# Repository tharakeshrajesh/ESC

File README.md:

# ESC
A probably not working electronic speed controller for a brushless direct current motor. <br>
It is rated for 12V and 20A (probably). <br>
<br>
__IT IS CURRENTLY UNTESTED SO TEST IT AT YOUR OWN WILL.__ <br>
<br>
I recommend reading all the README in each folder. **They are not all the same.**

## Some other info
This is a custom ESC made from scratch including a MOSFET half-bridge meant for brushless DC motors. Switches phases at high speeds. It takes in 12v and 20a from an XT60 male connector. You can program the STM microcontroller using the SWD header pins located on the board. There are two status LEDs (one on each side) to help with debugging if needed. The LED on the back of the board (D1) is connected to the gate driver fault pins so it will turn on if there is an error with the gate driver. The LED on the front (D3) is connected to the STM32 micocontroller and can be programmed for debugging or something (connected to pin 40). There are NO phase pads or bullet connectors located on the board for this revision so you will need to use alligator clips or something on the MOSFET source pins/body.

# Schematics

# PCB Previews

# Contact
email -> trajesh@3272010.xyz

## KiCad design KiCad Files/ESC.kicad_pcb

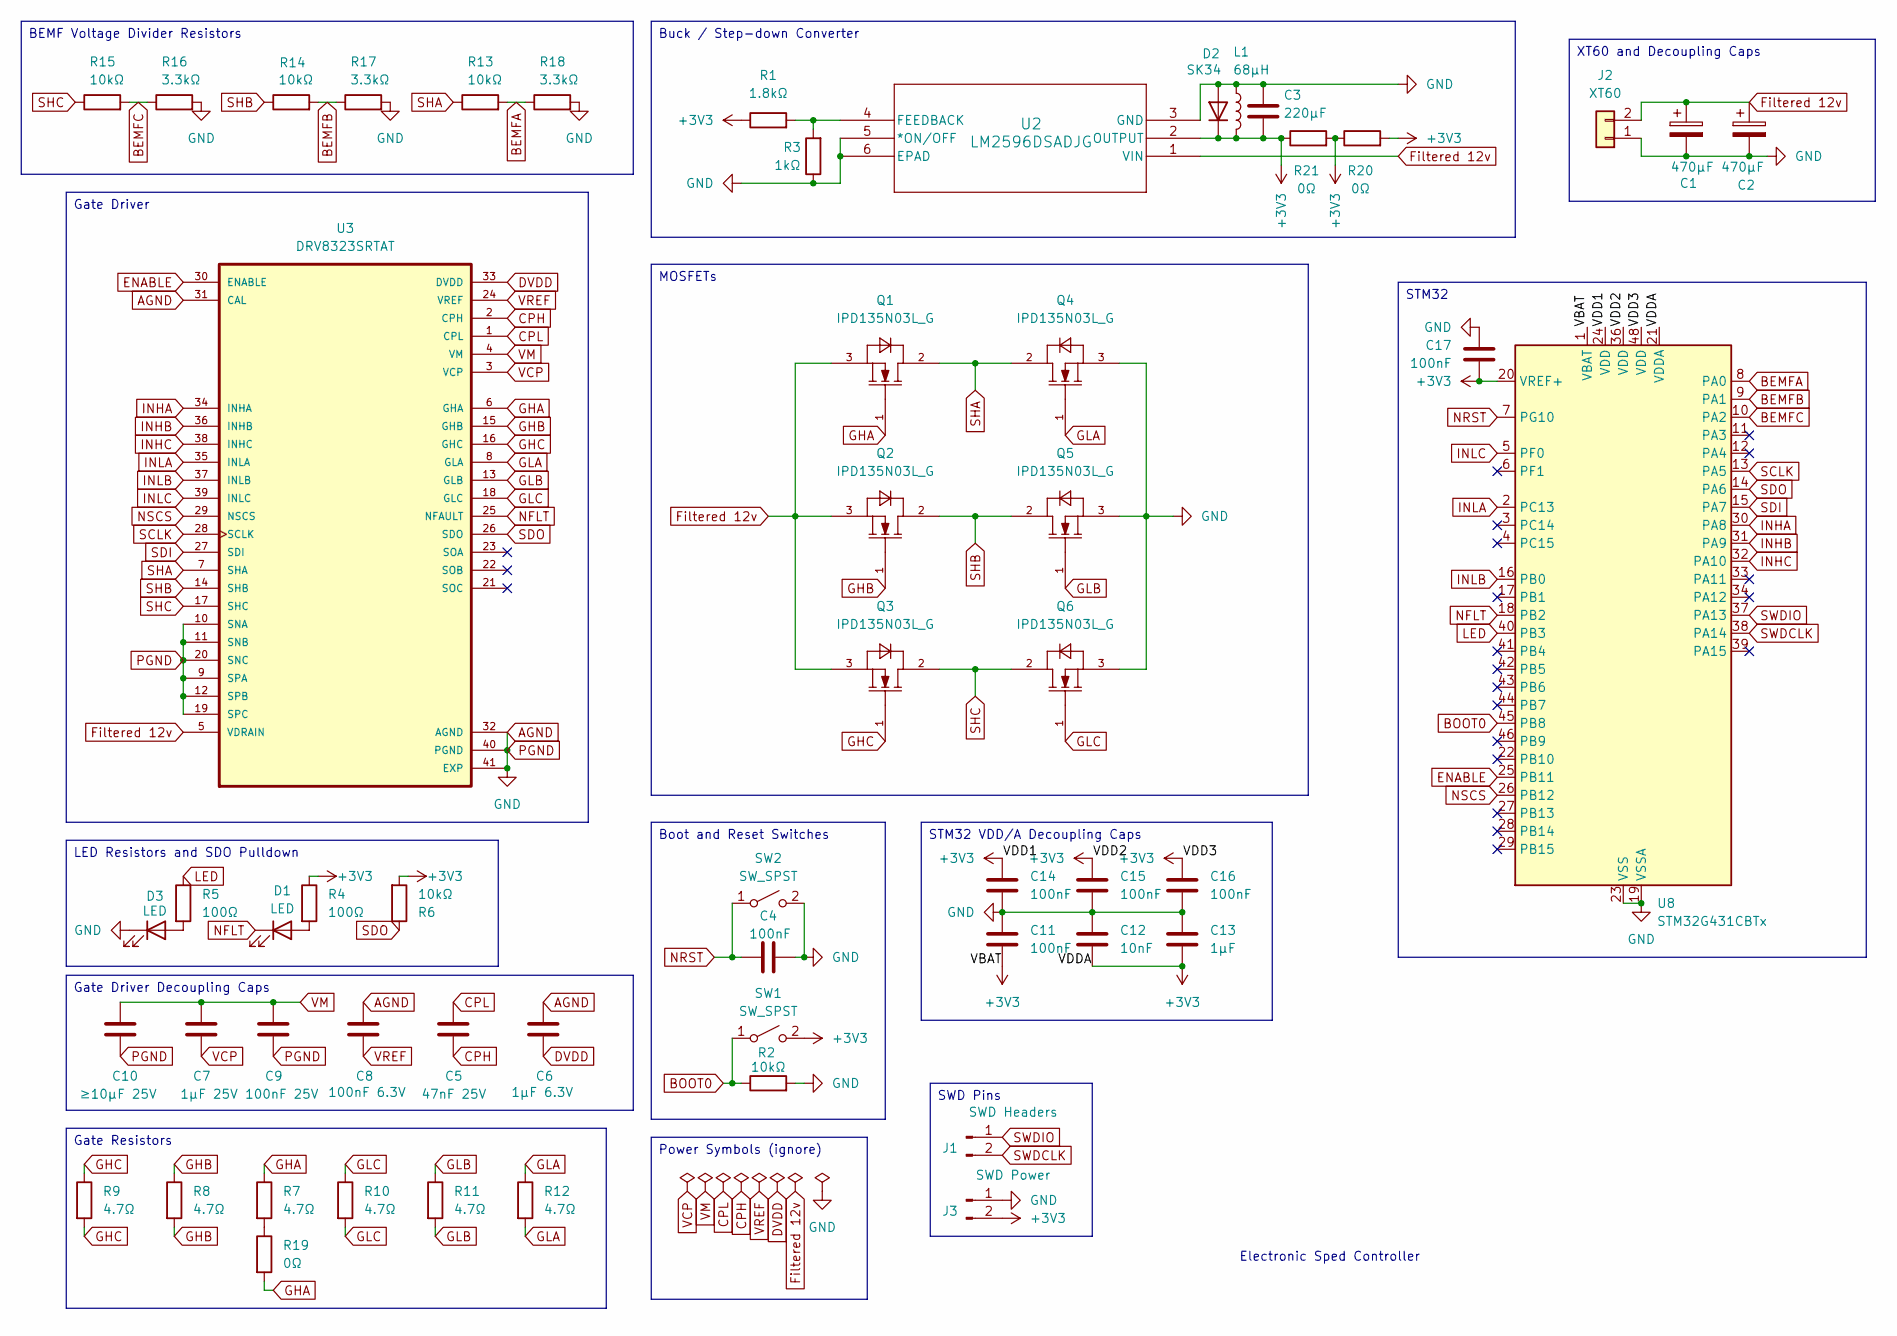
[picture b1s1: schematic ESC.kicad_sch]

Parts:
C1, C2: 470µF; CAP_ZSU_G16_PAN
C3: 220µF; C_1206_3216Metric
C4, C11, C14, C15, C16, C17: 100nF; C_0402_1005Metric
C5: 47nF 25V; C_0402_1005Metric
C6: 1µF 6.3V; C_0402_1005Metric
C7: 1µF 25V; C_0402_1005Metric
C8: 100nF 6.3V; C_0402_1005Metric
C9: 100nF 25V; C_0402_1005Metric
C10: ≥10µF 25V; C_0805_2012Metric
C12: 10nF; C_0603_1608Metric
C13: 1µF; C_0402_1005Metric
D1, D3: LED; LED_0603_1608Metric
D2: SK34; D_SMC
J1: SWD Headers; PinHeader_1x02_P2.54mm_Vertical
J2: XT60; AMASS_XT60PW-M_1x02_P7.20mm_Horizontal
J3: SWD Power; PinHeader_1x02_P2.54mm_Vertical
L1: 68µH; L_Bourns_SRR1260
Q1, Q2, Q3, Q4, Q5, Q6: IPD135N03L_G; TO228P998X235-3N-2-V
R1: 1.8kΩ; R_0603_1608Metric
R2, R6, R13, R14, R15: 10kΩ; R_0603_1608Metric
R3: 1kΩ; R_0603_1608Metric
R4, R5: 100Ω; R_0603_1608Metric
R7, R8, R9, R10, R11, R12: 4.7Ω; R_0402_1005Metric
R16, R17, R18: 3.3kΩ; R_0603_1608Metric
R19, R20, R21: 0Ω; R_0805_2012Metric
SW1, SW2: SW_SPST; SW_SPST_TL3305B
U2: LM2596DSADJG; D2PAK-5_ONS
U3: DRV8323SRTAT; QFN50P600X600X80-41N415X415; DigiKey_Part_Number 296-47095-1-ND
U8: STM32G431CBTx; LQFP48-7x7mm

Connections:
+3V3: C3.2, C11.2, C12.2, C13.2, C14.1, C15.1, C16.1, C17.1, D2.1 (K), J3.2, L1.2, R1.1, R4.1, R6.2, R20.1, R20.2, R21.1, R21.2, SW1.2 (B), U2.2 (OUTPUT), U8.1 (VBAT), U8.20 (VREF+), U8.21 (VDDA), U8.24 (VDD), U8.36 (VDD), U8.48 (VDD)
AGND: C1.2, C2.2, C3.1, C4.2, C6.1, C8.1, C9.2, C10.2, C11.1, C12.1, C13.1, C14.2, C15.2, C16.2, C17.2, D2.2 (A), D3.1 (K), J2.1, J3.1, L1.1, Q4.3, Q5.3, Q6.3, R2.2, R3.1, R16.2, R17.2, R18.2, SW2.2 (B), U2.3 (GND), U2.5 (*ON/OFF), U2.6 (EPAD), U3.9 (SPA), U3.10 (SNA), U3.11 (SNB), U3.12 (SPB), U3.19 (SPC), U3.20 (SNC), U3.31 (CAL), U3.32 (AGND), U3.40 (PGND), U3.41 (EXP), U8.19 (VSSA), U8.23 (VSS), U8.35 (VSS), U8.47 (VSS)
BEMFA: R13.2, R18.1, U8.8 (PA0)
BEMFB: R14.2, R17.1, U8.9 (PA1)
BEMFC: R15.2, R16.1, U8.10 (PA2)
BOOT0: R2.1, SW1.1 (A), U8.45 (PB8)
CPH: C5.2, U3.2 (CPH)
CPL: C5.1, U3.1 (CPL)
DVDD: C6.2, U3.33 (DVDD)
ENABLE: U3.30 (ENABLE), U8.25 (PB11)
Filtered 12v: C1.1, C2.1, J2.2, Q1.3, Q2.3, Q3.3, U2.1 (VIN), U3.5 (VDRAIN)
GHB: Q2.1, R8.1, R8.2, U3.15 (GHB)
GHC: Q3.1, R9.1, R9.2, U3.16 (GHC)
GLA: Q4.1, R12.1, R12.2, U3.8 (GLA)
GLB: Q5.1, R11.1, R11.2, U3.13 (GLB)
GLC: Q6.1, R10.1, R10.2, U3.18 (GLC)
INHA: U3.34 (INHA), U8.30 (PA8)
INHB: U3.36 (INHB), U8.31 (PA9)
INHC: U3.38 (INHC), U8.32 (PA10)
INLA: U3.35 (INLA), U8.2 (PC13)
INLB: U3.37 (INLB), U8.16 (PB0)
INLC: U3.39 (INLC), U8.5 (PF0)
LED: R5.1, U8.40 (PB3)
NFLT: D1.1 (K), U3.25 (NFAULT), U8.18 (PB2)
NRST: C4.1, SW2.1 (A), U8.7 (PG10)
NSCS: U3.29 (NSCS), U8.26 (PB12)
unnamed: D1.2 (A), R4.2
unnamed: D3.2 (A), R5.2
unnamed: R7.2, R19.1
unnamed: R1.2, R3.2, U2.4 (FEEDBACK)
SCLK: U3.28 (SCLK), U8.13 (PA5)
SDI: U3.27 (SDI), U8.15 (PA7)
SDO: R6.1, U3.26 (SDO), U8.14 (PA6)
SHA: Q1.2, Q4.2, R13.1, U3.7 (SHA)
SHB: Q2.2, Q5.2, R14.1, U3.14 (SHB)
SHC: Q3.2, Q6.2, R15.1, U3.17 (SHC)
SWDCLK: J1.2, U8.38 (PA14)
SWDIO: J1.1, U8.37 (PA13)
VCP: C7.2, U3.3 (VCP)
VM: C7.1, C9.1, C10.1, U3.4 (VM)
VREF: C8.2, U3.24 (VREF)

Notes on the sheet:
Electronic Sped Controller
XT60 and Decoupling Caps
Boot and Reset Switches
SWD Pins
Gate Resistors
STM32 VDD/A Decoupling Caps
STM32
MOSFETs
Buck / Step-down Converter
BEMF Voltage Divider Resistors
Power Symbols (ignore)
Gate Driver Decoupling Caps
LED Resistors and SDO Pulldown
Gate Driver

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
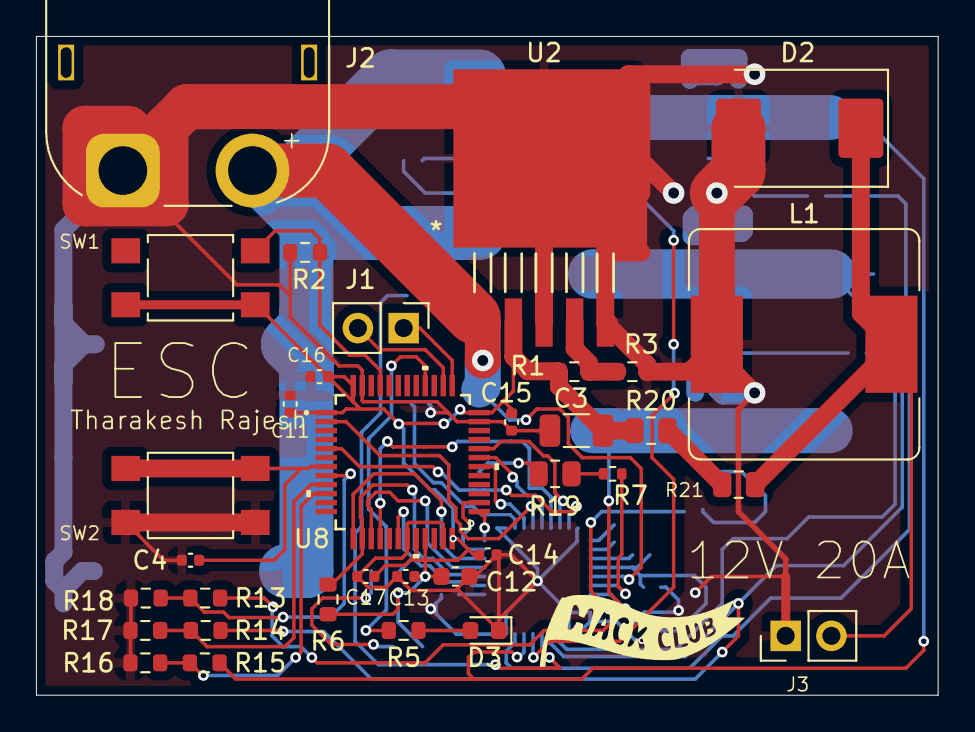
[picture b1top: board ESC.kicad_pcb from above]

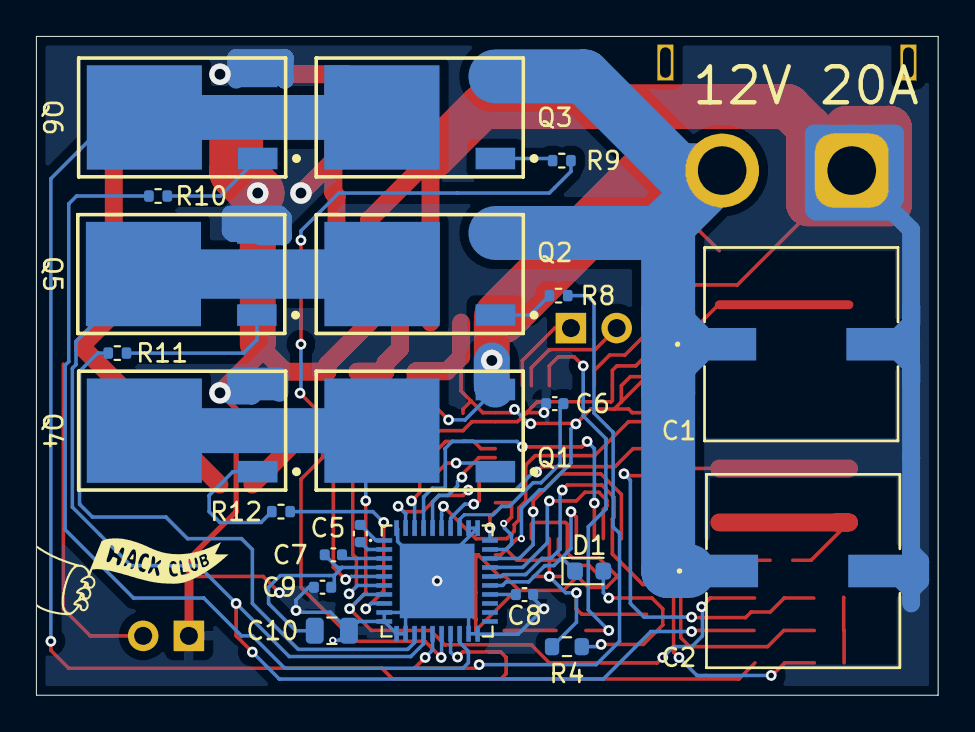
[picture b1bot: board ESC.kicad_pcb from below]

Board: 2 copper layers, 50.1 x 36.6 mm, 56 parts (22 on the bottom side), 43 nets.

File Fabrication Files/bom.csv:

Designator,Footprint,Quantity,Value,LCSC Part #
"C1, C2",CAP_ZSU_G16_PAN,2,470µF,C403803
C10,0805,1,≥10µF 25V,
"C11, C14, C15, C16, C17, C4",0402,6,100nF,C466234
C12,0603,1,10nF,
C13,0402,1,1µF,
C3,1206,1,220µF,
C5,0402,1,47nF 25V,
C6,0402,1,1µF 6.3V,
C7,0402,1,1µF 25V,
C8,0402,1,100nF 6.3V,
C9,0402,1,100nF 25V,
"D1, D3",0603,2,LED,
D2,D_SMC,1,SK34,C260396
J1,PinHeader_1x02_P2.54mm_Vertical,1,SWD Headers,
J2,AMASS_XT60PW-M_1x02_P7.20mm_Horizontal,1,XT60,
J3,PinHeader_1x02_P2.54mm_Vertical,1,SWD Power,
L1,L_Bourns_SRR1260,1,68µH,
"Q1, Q2, Q3, Q4, Q5, Q6",TO228P998X235-3N-2-V,6,IPD135N03L_G,C152614
R1,0603,1,1.8kΩ,
"R10, R11, R12, R7, R8, R9",0402,6,4.7Ω,
"R13, R14, R15, R2, R6",0603,5,10kΩ,
"R16, R17, R18",0603,3,3.3kΩ,
"R19, R20, R21",0805,3,0Ω,
R3,0603,1,1kΩ,
"R4, R5",0603,2,100Ω,
"SW1, SW2",SW_SPST_TL3305B,2,SW_SPST,C2886900
U2,D2PAK-5_ONS,1,LM2596DSADJG,C7419983
U3,QFN50P600X600X80-41N415X415,1,DRV8323SRTAT,C2150452
U8,LQFP48-7x7mm,1,STM32G431CBTx,C529355

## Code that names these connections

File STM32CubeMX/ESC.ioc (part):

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Mcu.Name=STM32G431C(6-8-B)Tx
Mcu.Package=LQFP48
Mcu.UserName=STM32G431CBTx
PA0.Mode=IN1-Single-Ended
PA0.Signal=ADC1_IN1
PA1.Mode=IN2-Single-Ended
PA1.Signal=ADC1_IN2
PA10.Signal=S_TIM1_CH3
PA11.Signal=S_TIM1_CH4
PA2.Mode=IN3-Single-Ended
PA2.Signal=ADC1_IN3
PA5.Mode=Full_Duplex_Master
PA5.Signal=SPI1_SCK
PA6.Mode=Full_Duplex_Master
PA6.Signal=SPI1_MISO
PA7.Mode=Full_Duplex_Master
PA7.Signal=SPI1_MOSI
PA8.Signal=S_TIM1_CH1
PA9.Signal=S_TIM1_CH2
PB0.Mode=Output Compare2 CH2 CH2N
PB0.Signal=TIM1_CH2N
PB12.Signal=GPIO_Output
PB13.Signal=GPIO_Output
PB2.Signal=GPIO_Input
PB3.Signal=GPIO_Output
PC13.GPIOParameters=GPIO_ModeDefaultPP,GPIO_Speed
PC13.GPIO_ModeDefaultPP=GPIO_MODE_AF_PP
PC13.GPIO_Speed=GPIO_SPEED_FREQ_LOW
PC13.Mode=PWM Generation1 CH1 CH1N
PC13.Signal=TIM1_CH1N
PF0-OSC_IN.Mode=Output Compare3 CH3 CH3N
PF0-OSC_IN.Signal=TIM1_CH3N
RCC.HSE_VALUE=8000000
RCC.SYSCLKFreq_VALUE=16000000
board=custom
